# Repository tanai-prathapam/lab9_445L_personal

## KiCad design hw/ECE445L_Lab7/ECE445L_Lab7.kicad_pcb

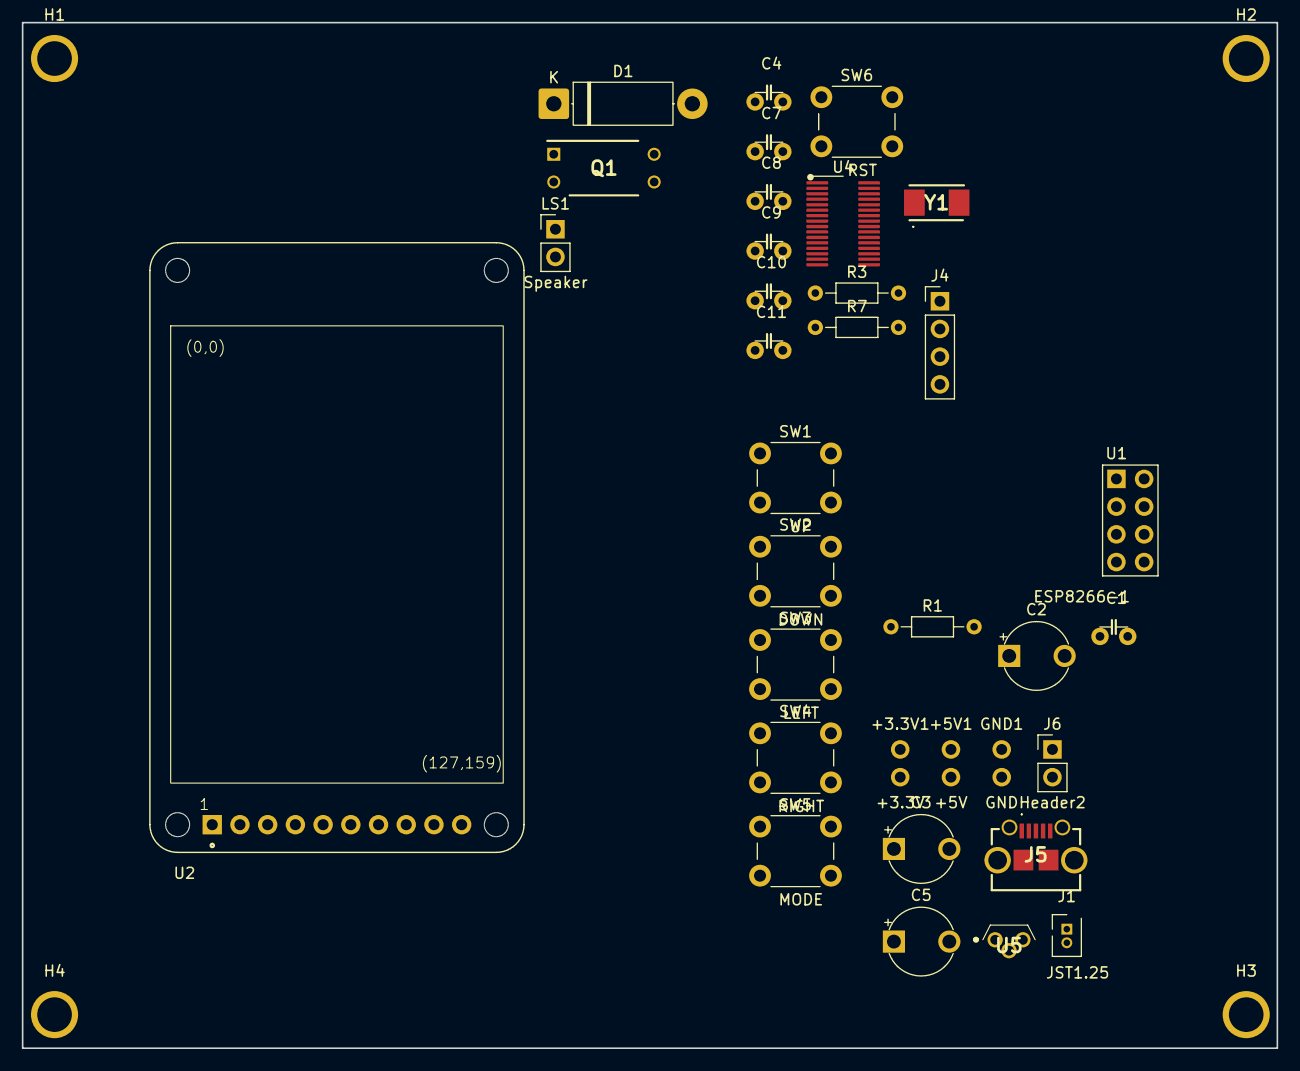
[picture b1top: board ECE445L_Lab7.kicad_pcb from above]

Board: 2 copper layers, 115.0 x 94.0 mm, 38 parts (0 on the bottom side), 12 nets, no tracks yet.

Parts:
+3.3V1: +3.3V; Testpoint_1x02_P2.54mm
+5V1: +5V; Testpoint_1x02_P2.54mm
C1: 100nF; C_Radial_100mil
C2, C3, C5: 4.7uF; CP_Radial_Tantal200mil
C4: 10nF; C_Radial_100mil
C7: 10uF; C_Radial_100mil
C8: 0.1uF; C_Radial_100mil
C9: 0.47uF; C_Radial_100mil
C10, C11: 10pF; C_Radial_100mil
D1: 1N914; D_5W_P12.70mm_Horizontal
GND1: GND; Testpoint_1x02_P2.54mm
H1, H2, H3, H4: MountingHole_4_40
J1: JST1.25; JST-1x02_1.25mm
J4: Debugger; PinHeader_1x04_P2.54mm_Vertical
J5: ZX62D-B-5PA8_30_; ZX62DB5PA830
J6: Header2; PinHeader_1x02_P2.54mm_Vertical
LS1: Speaker; PinHeader_1x02_P2.54mm_Vertical
Q1: IRLD024PBF; DIP920W60P254L490H457Q4N
R1: 10k; R_Axial_DIN0204_L3.6mm_D1.6mm_P7.62mm_Horizontal
R3: 47k; R_Axial_DIN0204_L3.6mm_D1.6mm_P7.62mm_Horizontal
R7: 100k; R_Axial_DIN0204_L3.6mm_D1.6mm_P7.62mm_Horizontal
SW1: UP; SW_PUSH_6mm
SW2: DOWN; SW_PUSH_6mm
SW3: LEFT; SW_PUSH_6mm
SW4: RIGHT; SW_PUSH_6mm
SW5: MODE; SW_PUSH_6mm
SW6: RST; SW_PUSH_6mm
U1: ESP8266-1; PinHeader_2x04_P2.54mm_Vertical
U2: Adafruit ST7735R; adafruit_st7735r2
U4: M0G3507QDGS32RQ1; VSSOP_0.5mm_32pin_handsolder
U5: LP2950-33LPRE3; TL431CLPM
Y1: 16MHz; ABM3

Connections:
+3V3: +3.3V1.1 (A), +3.3V1.2 (B), C5.1, C7.1, C8.1, D1.1 (K), J4.4 (C), LS1.1, R3.1, U4.7 (VDD), U5.1 (OUTPUT)
+5V: +5V1.1 (A), +5V1.2 (B), C3.1, J6.2 (B), U5.3 (INPUT)
GND: C3.2, C4.2, C5.2, C7.2, C8.2, C9.2, C10.2, C11.2, GND1.1 (A), GND1.2 (B), J1.2, J4.3 (C), J5.5, R7.1, SW1.1, SW2.1, SW3.1, SW4.1, SW5.1, SW6.1, U2.1 (GND_1), U4.8 (VSS), U5.2 (GND)
unnamed: D1.2 (A), LS1.2
unnamed: J1.1, J5.1, J6.1 (A)
unnamed: C4.1, R3.2, SW6.2, U4.6 (NRST)
unnamed: C9.1, U4.3 (VCORE)
PA2: R7.2, U4.9 (PA2/ROSC)
PA5/HFXIN: C10.1, U4.12 (PA5/HFXIN/FCC_IN), Y1.1
PA6/HFXOUT: C11.1, U4.13 (PA6/HFCLK_IN/HFXOUT), Y1.2
SWCLK: J4.2 (B), U4.27 (PA20/SWCLK)
SWDIO: J4.1 (A), U4.26 (PA19/SWDIO)
